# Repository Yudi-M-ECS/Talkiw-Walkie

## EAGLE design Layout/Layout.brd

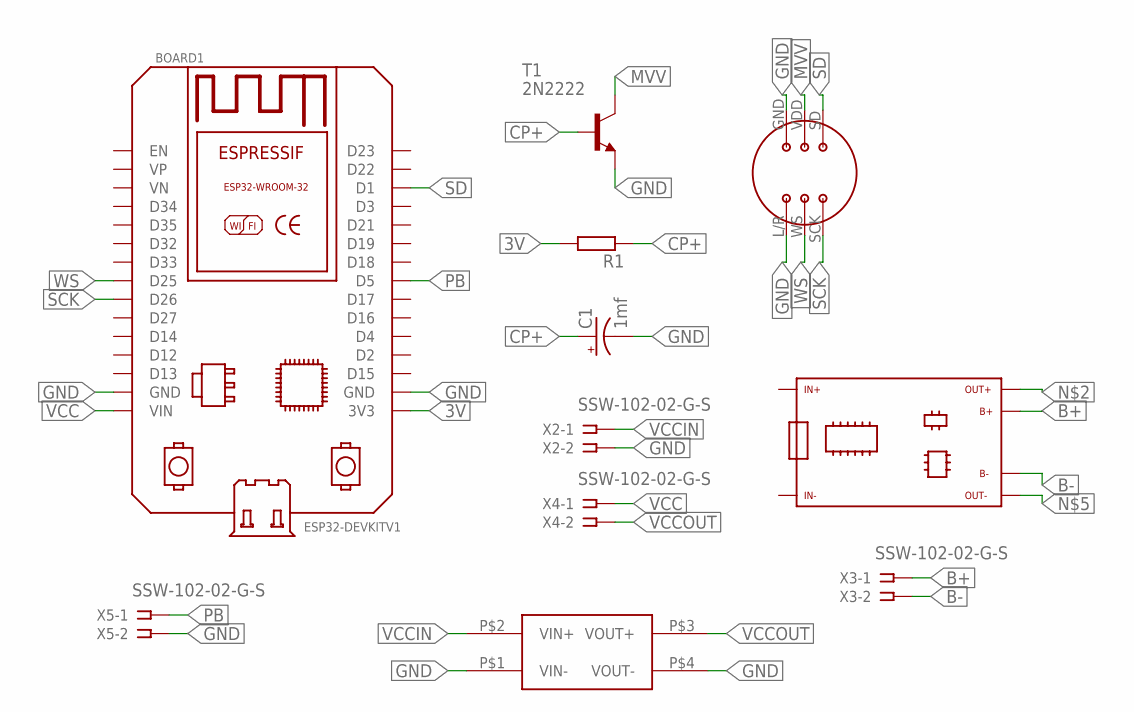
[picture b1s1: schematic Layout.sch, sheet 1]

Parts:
BOARD1: ESP32DEVKITV1; ESP32-DEVKITV1
C1: 1mf; CPOL-RADIAL-5MM-10MM-KIT
CHARGER_HW-1: CHARGER_HW-107
INMP1: INMP441
R1: R-EU_0204/7; 0204/7
T1: 2N2222; TO18
U$2: MP1584-MINI-SMD; MINI-DC-BRICK-SMD
X2, X3, X4, X5: SSW-102-02-G-S

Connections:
3V: BOARD1.3V3, R1.2
B+: CHARGER_HW-1.B+, X3.1
B-: CHARGER_HW-1.B-, X3.2
CP+: C1.+, R1.1, T1.2 (B)
GND: BOARD1.GND, BOARD1.GND@1 (GND), C1.-, INMP1.GND, INMP1.L/R, T1.1 (E), U$2.P$1 (VIN-), U$2.P$4 (VOUT-), X2.2, X5.2; also elsewhere on the board
MVV: INMP1.VDD, T1.3 (C)
PB: BOARD1.D5, X5.1
SCK: BOARD1.D26, INMP1.SCK
SD: BOARD1.D1, INMP1.SD
VCC: BOARD1.VIN, X4.1; also elsewhere on the board
VCCIN: U$2.P$2 (VIN+), X2.1
VCCOUT: U$2.P$3 (VOUT+), X4.2
WS: BOARD1.D25, INMP1.WS

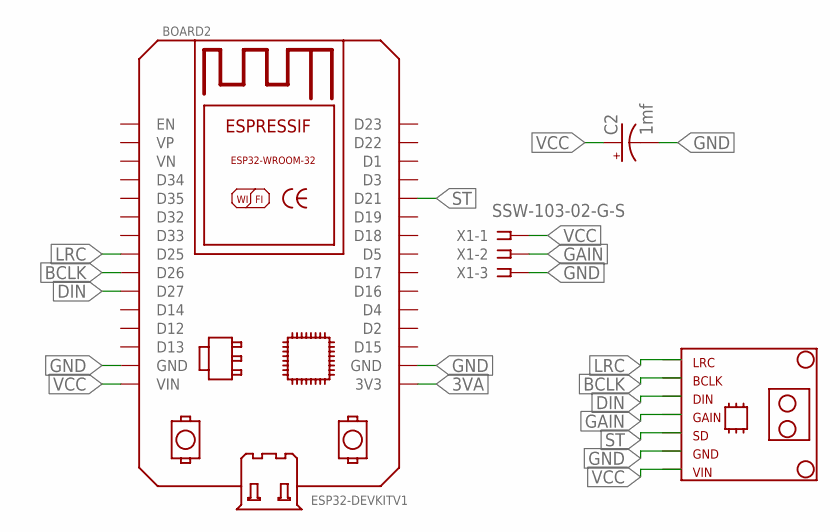
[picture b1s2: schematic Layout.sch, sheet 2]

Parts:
BOARD2: ESP32DEVKITV1; ESP32-DEVKITV1
C2: 1mf; CPOL-RADIAL-5MM-10MM-KIT
MAX98357A1: MAX98357A
X1: SSW-103-02-G-S

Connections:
3VA: BOARD2.3V3
BCLK: BOARD2.D26, MAX98357A1.BCLK
DIN: BOARD2.D27, MAX98357A1.DIN
GAIN: MAX98357A1.GAIN, X1.2
GND: BOARD2.GND, BOARD2.GND@1 (GND), C2.-, MAX98357A1.GND, X1.3; also elsewhere on the board
LRC: BOARD2.D25, MAX98357A1.LRC
ST: BOARD2.D21, MAX98357A1.SD
VCC: BOARD2.VIN, C2.+, MAX98357A1.VIN, X1.1; also elsewhere on the board

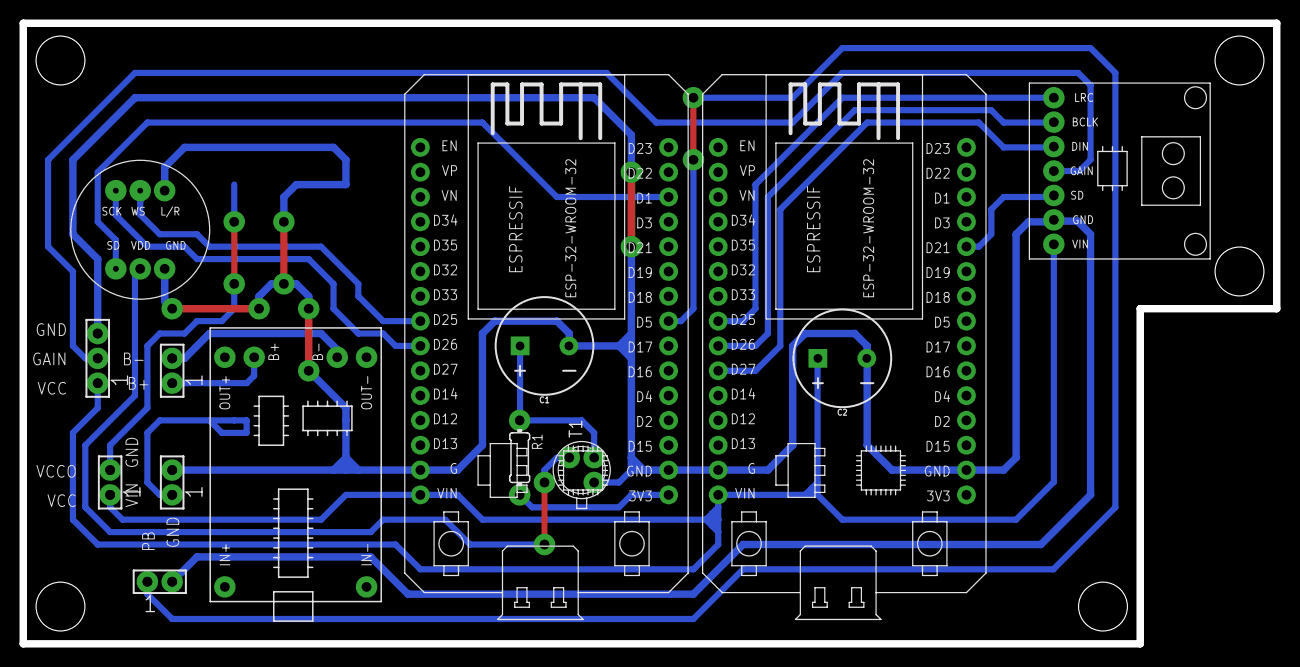
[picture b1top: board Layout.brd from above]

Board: 2 copper layers, 128.3 x 63.5 mm, 15 parts (1 on the bottom side), 18 nets.

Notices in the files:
parts and their libraries:
SparkFun-Capacitors: Licensing: Creative Commons ShareAlike 4.0 International - https://creativecommons.org/licenses/by-sa/4.0
